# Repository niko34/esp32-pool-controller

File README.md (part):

<h1> ESP32 Pool Controller</h1>

Disclaimer : projet en cours de construction.

Contrôleur automatique de piscine basé sur ESP32 :
- mesure : température, pH, ORP
- pilotage : pompe de filtration, éclairage
- correction avec pompes doseuses : pH et ORP
- interfaces : application web locale, MQTT, API

## 🎯 Fonctionnalités

### Mesures et Contrôle
- **pH** : Mesure via module numérique Atlas Scientific **EZO pH** (I²C). La température de l'eau est transmise au module pour la compensation de température de la mesure.
- **ORP (Redox)** : Mesure via module numérique Atlas Scientific **EZO ORP** (I²C)
- **Température** : Deux sondes Dallas **DS18B20** (eau + circuit/boîtier), identification automatique des rôles sur le bus OneWire
- **Historique** : Historique des mesures
- **Mode d'installation** : Décrit le câblage réel du contrôleur et garantit qu'aucun produit n'est injecté sans circulation d'eau — *PoolController pilote la filtration* (sortie 12 V), *Alimenté par le circuit de filtration*, ou *Filtration externe signalée* (une domotique tierce signale l'état via HTTP/MQTT ; dosage suspendu sans signal récent)
- **Filtration** : Programmation automatique en fonction de la température de l'eau, programmation horaire, manuel
- **Eclairage** : Programmation horaire, manuel
- **Régulation automatique de pH et ORP** : Injection de produit de correction (pH-, chlore liquide) par **régulation proportionnelle temporisée (P)** avec pause de mélange et contrôle de débit PWM. Les mesures sont **lissées** (médiane + EMA) avant d'alimenter la régulation. *(pH+ : option de configuration présente mais non gérée actuellement.)*
- **Consommation de produits** : Estimation de la consommation de produit
- **Application Web locale** : Configuration et visualisation temps réel. Accessible sur le réseau Wifi configuré (`http://poolcontroller.local`) ou un réseau Wifi de en mode point d'accès (`http://192.168.4.1`). Aucune dépendance au Cloud. [Voir les screenshots](screenshots/)
- **API** : Toutes les fonctionnalités sont exposées avec une API
- **MQTT** : Exposition des données sur MQTT. Auto-discovery HomeAssistant.
- **Mise à jour OTA** : Mise à jour firmware via interface web

### Sécurité
- ⚠️ **Limites journalières** : Protection contre le surdosage
- ⚠️ **Limites horaires** : Temps maximum d'injection par heure configurable
- ⚠️ **Watchdog** : Redémarrage automatique en cas de blocage du système (30s)
- ⚠️ **Alertes MQTT** : Notifications en cas d'anomalie

## 📋 Matériel Requis

### Module ESP32 — ⚠️ PSRAM requise

Utiliser un **ESP32-DevKitC-VE** (module **WROVER-E**, ESP32 classique **avec 8 Mo de PSRAM**) — cf. `kicad/esp32-pool-controller/BOM.xlsx`, repère U2.

> ⚠️ **Pourquoi la PSRAM est nécessaire** : la **mise à jour en ligne depuis GitHub**
> (onglet Système → « Vérifier les mises à jour ») ouvre une session TLS qui réclame
> plusieurs blocs de mémoire contigus d'environ 16 Ko. Sur un module **sans PSRAM**
> (WROOM-32), la RAM interne ne les fournit plus de façon fiable une fois le système
> démarré : la vérification échoue de manière intermittente (`BIGNUM - Memory
> allocation failed`). Avec la PSRAM, ces allocations y sont placées automatiquement
> (seuil 4 Ko) et la fonction redevient fiable.
>
> Le firmware **fonctionne** sur un WROOM-32 sans PSRAM (binaire unique, détection
> automatique au démarrage, dégradation gracieuse — depuis la v2.18.0) : régulation,
> interface web, MQTT et **mise à jour manuelle par upload de fichier** restent
> pleinement opérationnels. Seule la vérification/installation automatique depuis
> GitHub est concernée.
>
> Modules déconseillés : l'**ESP32-S3** n'est pas supporté (architecture différente,
> brochage incompatible avec le PCB v2 — les GPIO 22 et 25 utilisés par l'I²C et la
> pompe pH n'y existent pas).

### PCB

Les **sources** KiCad sont versionnées dans [`kicad/`](kicad/) :

- [Schéma électronique](screenshots/Schema.png)
- [PCB](screenshots/PCB.png)
- `kicad/esp32-pool-controller/esp32-pool-controller.kicad_sch` — schéma
- `kicad/esp32-pool-controller/esp32-pool-controller.kicad_pcb` — routage
- `kicad/esp32-pool-controller/BOM.xlsx` — nomenclature (source ; le `BOM.csv`
  s'en déduit avec `python3 tools/bom_export.py`)

Les **fichiers de fabrication** (gerbers, perçage) ne sont pas versionnés : ils se
régénèrent avec `./scripts/build-gerbers.sh` (carte v2) ou `./scripts/build-jlcpcb.sh` (cartes v3, avec la liste des pièces et les positions) et sont publiés comme assets des
releases `pcb-vX`. Voir « Fichiers générés et releases » dans `CLAUDE.md`.

### Boîtier

Le boîtier imprimé en 3D est décrit par un script qui le construit en entier : voir [`boitier/`](boitier/README.md). Les fichiers FreeCAD, STEP et STL qu'il produit ne sont pas versionnés ; ils se régénèrent.

## 🧭 Reprendre le projet

Cette section s'adresse à quiconque récupère le dépôt — y compris son auteur dans
deux ans. Elle dit **où est quoi** et **comment on travaille ici**.

### Outils nécessaires

| Outil | Pour quoi | Indispensable ? |
|---|---|---|
| **PlatformIO** | compiler, téléverser, lancer les tests | oui |
| **Node.js** | `minify.js`, appelé par `build_fs.sh` | oui |
| **Chrome / Chromium** | générer les PDF de documentation | pour les releases |
| **`gh`** (GitHub CLI) | publier les releases | pour les releases |
| **KiCad 7+** | ouvrir le PCB, générer les gerbers | pour le matériel |
| **Python 3** | `tools/*.py` (BOM, coredump, couverture) | ponctuel |

⚠️ Sur macOS, `kicad-cli` et Chrome ne sont pas dans le `PATH` : les scripts
`scripts/*.sh` sondent aussi les emplacements `.app`.

### Repartir d'un clone (conteneur, autre machine)

```bash
# Debian / Ubuntu
sudo apt install -y python3 python3-pip nodejs npm chromium imagemagick zip gh
pip install --user platformio
# facultatif, seulement pour le PCB :
sudo apt install -y kicad

git clone https://github.com/niko34/esp32-pool-controller.git
cd esp32-pool-controller
pio pkg install -e esp32dev_core3   # télécharge la plateforme et les libs
pio test -e native                  # doit être vert
pio run                             # doit compiler
```

**Ce qui fonctionne depuis un clone nu** : les agents, les skills et les
commandes, les specs, les tests natifs, la compilation, la génération des PDF et
celle des gerbers. **Trois workflows GitHub Actions rejouent les trois premiers à
chaque push et à chaque PR** — tests natifs + couverture, compilation
`pio run -e esp32dev_core3`, et hygiène des specs (`./tools/check_specs.sh`,
lançable en local) : ce n'est pas une promesse, c'est une preuve. Voir
[docs/BUILD.md](docs/BUILD.md#intégration-continue-github-actions). Les scripts détectent leurs outils et échouent avec un message explicite
si l'un manque.

**Ce qui ne fonctionne pas à distance** : le déploiement sur l'appareil. Son mot
de passe n'est pas dans le dépôt — délibérément — et il vit sur un réseau local.
Il faut être sur le même réseau, et fournir le mot de passe :

```bash
./ota_update.sh firmware <adresse-ip> <mot-de-passe>
```

**Confort dégradé** : `.claude/settings.local.json` n'est pas versionné (il
contient des chemins absolus propres à une machine). Le `settings.json` partagé
couvre l'essentiel — y compris les garde-fous `deny` et `ask` — mais vous
confirmerez plus de commandes qu'en local. C'est le prix d'une configuration
qui ne présume rien de la machine.

### Où est quoi

```
src/            firmware C++ (ESP32, Arduino)      data/     interface web (vanilla JS)
test/           tests natifs — logique pure         docs/     doc technique, ADR, guides
specs/          LA SOURCE DE VÉRITÉ des demandes    kicad/    sources du PCB
scripts/        livrables de release (PDF, gerbers) tools/    utilitaires de développement
.claude/        agents, skills et commandes         builds/   archive LOCALE des binaires
```

### Comment on travaille

Le cycle est décrit en détail dans **[CLAUDE.md](CLAUDE.md)**. En résumé :

1. **Une demande = une spec** dans `specs/features/todo/`, au format du template.
   Elle se déplace vers `doing/` quand le travail commence, `done/` quand il finit,
   enrichie des notes techniques et des décisions prises.
2. **Le travail passe par des agents spécialisés** (`.claude/agents/`) :
   conception, implémentation firmware ou web, tests, revue, documentation.
   ⚠️ **`pool-chemistry` est obligatoire** dès qu'on touche au dosage, à la
   régulation ou à la calibration des sondes — ce sont les pompes qui injectent de
   l'acide et du chlore dans un bassin.
3. **Les tests natifs sont non négociables** : `pio test -e native` doit rester
   vert, et tout test neuf est **validé par mutation** — on casse volontairement le
   code qu'il protège pour vérifier qu'il meurt. Plusieurs défauts réels de ce
   projet n'ont été trouvés que comme ça.
4. **Toute décision structurante devient un ADR** dans `docs/adr/`. Les ADR sont
   immuables : on les amende d'une bannière, on ne réécrit pas leur histoire.

### Les commandes utiles

```bash
pio run                    # compiler (env unique esp32dev_core3)
pio test -e native         # 33 suites, ~1 286 cas
./build_fs.sh              # construire le filesystem web
./deploy.sh all            # flasher par USB (firmware + filesystem)
./deploy.sh ota-firmware   # mettre à jour par WiFi
./tools/coverage.sh        # couverture des tests
/release                   # publier une version firmware + doc
/release-pcb               # publier des fichiers de fabrication PCB
```

Il n'y a **qu'un seul environnement matériel**, `esp32dev_core3`. L'ancien repli
core Arduino 2.x a été retiré en v2.42.1 : il n'était plus compilable, plus
flashable, et aucun binaire de secours n'avait jamais été archivé
([ADR-0069](docs/adr/0069-retrait-repli-core-2.md)).

### Ce qui n'est pas dans le dépôt, et pourquoi

Les **fichiers générés** n'y sont pas : PDF de documentation, gerbers de
fabrication, firmware compilé. Ils sont attachés aux **releases GitHub**, où ils
sont horodatés et associés à un tag. Voir « Fichiers générés et releases » dans
[CLAUDE.md](CLAUDE.md).

**Deux exceptions volontaires**, parce que ces fichiers ne sont pas *générés* mais
*relevés* — rien ne les régénère :

- **`docs/incidents/`** — les coredumps de production et leurs traces décodées. Un
  coredump n'existe qu'une fois : il est écrasé au crash suivant.
- **L'ELF est attaché à chaque release** (~29 Mo) en plus du `.bin`. `esp-coredump`
  vérifie le SHA256 de l'image et refuse un ELF qui ne correspond pas : sans celui
  de la version exacte, un crash reste indéchiffrable.

`builds/` contient l'archive **locale** des ELF de tous les builds (2,6 Go) et
n'est pas versionné.

Le **générateur du boîtier** est dans [`boitier/`](boitier/README.md) ; ses sorties (FreeCAD, STEP, STL) ne sont pas versionnées.

## 🚀 Installation

### PlatformIO (Recommandé)

1. **Cloner le projet**
   ```bash
   git clone https://github.com/niko34/esp32-pool-controller.git
   cd esp32-pool-controller
   ```

2. **Ouvrir avec VS Code + PlatformIO**
   ```bash
   code .
   ```

3. **Compiler et déployer**

   L'unique environnement de build est **`esp32dev_core3`** (core Arduino 3.x / ESP-IDF 5 via pioarduino) — bootloader **et** application, depuis la v2.20.4 ([ADR-0042](docs/adr/0042-core3-environnement-par-defaut.md)). L'environnement de repli core 2 a été retiré en v2.42.1 ([ADR-0069](docs/adr/0069-retrait-repli-core-2.md)) :

   ```bash
   pio run                              # core 3, env unique
   ./deploy.sh all                      # firmware + filesystem
   ```

   ℹ️ Premier build sur une machine neuve : `pio pkg install -e esp32dev_core3` (téléchargement du framework). Voir [BUILD.md](docs/BUILD.md#lenvironnement-firmware-unique).

   **Via USB** (obligatoire pour la première installation, et pour tout changement de bootloader ou de table de partitions) :
   ```bash
   ./deploy.sh all       # Compile et upload firmware + filesystem
   ./deploy.sh firmware  # Firmware uniquement
   ./deploy.sh fs        # Filesystem uniquement
   ```

   **Via WiFi OTA** (mises à jour suivantes, une fois la première installation USB effectuée) :
   ```bash
   ./deploy.sh ota-all       # Compile et envoie firmware + filesystem
   ./deploy.sh ota-firmware  # Firmware uniquement
   ./deploy.sh ota-fs        # Filesystem uniquement
   ```

   Voir [UPDATE_GUIDE.md](docs/UPDATE_GUIDE.md) pour plus de détails sur les méthodes de mise à jour.

4. **Moniteur série**
   ```bash
   pio device monitor -b 115200
   ```

### Première connexion et accès à l'interface Web

1. **Première connexion**
   - Au démarrage, l'ESP32 crée un point d'accès WiFi `PoolControllerAP`
   - Le mot de passe WiFi AP est **unique par appareil**, généré aléatoirement au premier boot et stocké en NVS
   - Il s'affiche en clair dans le moniteur série **tant que le wizard de configuration n'est pas complété** :
     ```
     [INFO] AP démarré: PoolControllerAP
     [INFO] AP Password: XXXXXXXX
     [INFO] IP AP: 192.168.4.1
     ```
   - Le flash USB (`./deploy.sh all`) **enchaîne le moniteur série** : l'ouverture du port redémarre l'ESP32, le boot est donc capté depuis sa première ligne, sans manœuvre particulière
   - Coller le mot de passe sur une étiquette sur le boîtier
   - Se connecter au réseau `PoolControllerAP` avec ce mot de passe et accéder à l'assistant de configuration http://192.168.4.1

   > **Après le wizard complété**, si l'AP redémarre (ex : perte WiFi), le mot de passe n'est plus affiché en clair dans les logs pour des raisons de sécurité. Utiliser l'étiquette ou l'API :
   > ```
   > GET http://poolcontroller.local/auth/ap-password
   > ```

   > **Forcer la génération d'un nouveau mot de passe AP** (ex : fabrication d'un nouvel appareil, remplacement d'étiquette) : utiliser l'option `factory`, qui efface la flash, réinstalle, ré-efface la NVS **en dernier**, puis **ouvre le moniteur série automatiquement**. Le mot de passe s'affiche dans les premières lignes de boot — inutile d'ouvrir un moniteur à la main, et inutile de le lancer *avant* d'alimenter l'appareil.
   > ```bash
   > ./deploy.sh factory
   > ```
   > ```
   > === MOT DE PASSE AP WIFI: XXXXXXXX ===
   > ```
   > ⚠️ Efface **toute** la flash (firmware, filesystem, NVS, historique). À n'utiliser que sur un appareil qu'on réinitialise complètement. Voir [UPDATE_GUIDE.md](docs/UPDATE_GUIDE.md#récupérer-le-mot-de-passe-wifi-ap).

2. **Accès interface web**
   - `http://poolcontroller.local` si réseau wifi configuré, sinon se connecter au réseau AP PoolControllerAP et utiliser l'adresse http://192.168.4.1
   - Onglets disponibles:
     - **Tableau de bord** : Visualisation temps réel pH/ORP/Température
     - **Filtration** : Contrôle et programmation de la pompe de filtration
     - **Éclairage** : Contrôle et programmation de l'éclairage
     - **Température** : Historique et calibration de la sonde de température
     - **pH** : Mesure, historique, calibration et réglages dosage pH
     - **ORP** : Mesure, historique, calibration et réglages dosage chlore
     - **Produits** : Suivi de la consommation des produits chimiques
     - **Paramètres** : WiFi, MQTT, heure, sécurité, régulation, système

### Calibration Capteurs

#### Calibration pH (Atlas Scientific EZO pH)

La calibration est gérée **en interne par le module EZO** (commandes I²C `Cal,...`), mémorisée dans le module lui-même — il n'y a ni offset/pente stockés côté ESP32, ni EEPROM, ni librairie analogique. Elle se déclenche depuis l'interface web, onglet **pH** → carte **Calibration** (deux sous-blocs indépendants). Le module EZO pH accepte les points **milieu (pH 7.0)**, **bas (pH 4.0)** et, optionnellement, **haut**. La régulation automatique du pH est **inhibée tant que les 2 points (mid + low) ne sont pas calibrés**.

**Calibration via l'interface web** :
1. Aller dans l'onglet **pH** → carte **Calibration**
2. Rincer la sonde à l'eau distillée, la plonger dans la solution tampon **pH 7.00**, attendre stabilisation (~1 min)
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
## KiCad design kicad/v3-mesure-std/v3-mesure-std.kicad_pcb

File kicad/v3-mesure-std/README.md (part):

# Carte de mesure du PCB v3, à composants courants — composants et connexions

Carte de mesure **retenue pour le v3** (décision D8 de
[feature-215](../../specs/features/todo/feature-215-conception-du-pcb-v3.md), 2026-11-25) :
sans module Atlas, tous les composants posés par l'atelier, chacun avec un équivalent d'un
autre fabricant. L'étude et les relectures sont dans
[feature-217](../../specs/features/todo/feature-217-carte-de-mesure-a-composants-courants.md).

La première étude, à modules Atlas (`kicad/v3-mesure/`), a été **retirée du dépôt le
2026-11-26** : elle reste dans l'historique git (dernier état : commit `5eb6b3d`). Ce qui en
restait valable est recopié plus bas, dans « Repris de l'étude à modules Atlas ».

✅ **État au 2026-11-25 : schéma (rév. 0.2) et carte placée et routée (rév. 0.1) écrits par
script, relus par `electronics-reviewer` — aucune erreur. Pas encore ouverts dans KiCad par
l'utilisateur.**

🆕 **Rév. 0.3 du 2026-11-28 — étude des parasites et de la fiabilité** (demande de l'utilisateur).
Quatre changements sur l'entrée de chaque voie, détaillés en fin de fiche : un **filtre devant le
convertisseur**, le **corps de la prise protégé des décharges**, la **garde pilotée à travers une
résistance et découverte de son vernis**, et l'**alimentation de l'amplificateur pH filtrée**.
Les règles à tenir désormais, avec leurs raisons, sont dans
[`../REGLES-CEM-ET-FIABILITE.md`](../REGLES-CEM-ET-FIABILITE.md) ;
`python3 scripts/verifier_regles_cartes.py v3-mesure-std` les contrôle.
Schéma et carte sont tous deux en rév. 0.3, régénérés par leurs scripts.

## Les fichiers de ce dossier

| Fichier | Rôle |
|---|---|
| `generer_schema.py` | écrit le schéma depuis le tableau ci-dessous. ⚠️ Le relancer **réécrit** le schéma en entier |
| `v3-mesure-std.kicad_sch` | le schéma, format A2 : les deux voies à gauche, le connecteur J1 à droite |
| `v3-mesure-std.kicad_sym`, `sym-lib-table` | les symboles propres à la carte |
| `generer_carte.py` | écrit la carte depuis la netlist du schéma : placement, pistes, plans. ⚠️ Le relancer **réécrit** la carte en entier |
| `v3-mesure-std.kicad_pcb` | la carte, 73 × 54 mm, quatre couches |
| `v3-mesure-std.pretty/`, `fp-lib-table` | empreintes propres : module d'alimentation, prise BNC, trou de fixation |
| `v3-mesure-std.kicad_pro`, `v3-mesure-std.kicad_dru` | le projet, ses classes de fils et ses règles d'isolement |

Pour régénérer :
`kicad-cli sch export netlist -o /tmp/n.net v3-mesure-std.kicad_sch` puis
`python3 generer_carte.py /tmp/n.net`.

## La carte (2026-11-25)

Même contour que la carte à modules Atlas : 73 × 54 mm, prises BNC à l'entraxe de 36,3 mm
sur le bord du bas, J1 en haut, quatre trous M3. Couches : composants et signaux dessus,
masse au-dessous, alimentation, puis masse et quelques pistes sur la face du dessous.

**La barrière d'isolation**
- Zone interdite au cuivre de **3,0 mm** sur les quatre couches entre le côté ESP32 et chaque
  voie : c'est la distance entre les deux rangées de pastilles de l'ISO1540.
- Au droit du module d'alimentation elle se réduit à un col : ses broches 2 et 3 sont au pas
  de 2,54 mm, soit **0,94 mm de cuivre à cuivre**, que rien ne peut élargir.
- Entre la voie pH et la voie ORP : 3,0 mm.
- ℹ️ La carte à modules Atlas avait 5 mm partout (imposés par l'ADM3260). Ici la barrière
  est **fonctionnelle** : elle ne voit que quelques volts, la sécurité secteur vient de
  l'alimentation (D4). 1 500 V est l'essai d'une minute du module. Relu et jugé cohérent.

**L'entrée de la sonde**
- pH : anneau de garde sur le dessus, relié aux broches 2 et 7 de U104, qui entoure l'âme de
  la prise, R105 et la broche 1 ; garde en plein sur les trois autres couches, sous l'entrée.
  Piste d'entrée de 2,1 mm, piste de l'âme de 6,1 mm.
- ORP : même anneau, relié à `MESURE_ORP`, refermé sous le boîtier entre la broche 4 (masse)
  et la broche 5 (entrée).
- ~~**Vernis conservé** sur l'anneau et l'entrée (point P6 fermé).~~ ⚠️ **Revu le 2026-11-28
  (rév. 0.3) : le vernis est retiré sur la garde**, là où rien n'est posé dessus. Le calcul
  d'origine (0,0003 pH pour 1 GΩ de fuite) supposait que la fuite allait vers la garde. Or une
  fuite **en surface du vernis** passe par-dessus un anneau enterré sans le rencontrer, et va de
  l'âme au corps de la prise : avec 1 GΩ et une sonde de 250 MΩ, c'est 20 % d'erreur de pente.
  Le fabricant de l'amplificateur le demande (fiche du LMP7721, § 10.1 : pas de vernis sur
  l'entrée ni sur la garde). Le cuivre découvert est doré par l'atelier, il n'est pas nu.
  ⛔ Aucune ouverture sous la prise, côté dessus : son corps métallique y est posé.
- **Rév. 0.3** : l'amplificateur et la résistance d'entrée sont remontés de 1,5 mm. La pastille
  « âme » de R105 était à 0,58 mm du corps de la prise ; elle en est à 2,1 mm (1,78 mm de son
  encombrement dessiné). Deux doigts de garde descendent de l'anneau entre l'âme et le corps.
- Le trait d'encre de la prise BNC qui passait sur l'âme et l'anneau est retiré de l'empreinte.
- Le corps de la prise est relié par une zone de cuivre `REF` sur le dessus.

**Deux pistes passent par la face du dessous** : SCL côté isolé, sur 3 mm, pour croiser
SDA ; et, sur la voie ORP, la liaison de R208 au corps de la prise. Sans effet sur la mesure.

### Ce qui est vérifié
- Contrôle des règles (`kicad-cli pcb drc --severity-all --schematic-parity`) : 0 violation,
  0 liaison manquante, 0 écart avec le schéma. Les seuls messages portent sur des
  bibliothèques absentes de la machine de génération.
- Les protections ont été éprouvées par des fautes volontaires : via dans la barrière,
  condensateur non relié, piste qui franchit la barrière, court-circuit masse / entrée du pH
  — toutes détectées. ℹ️ Un plan de cuivre débordant sur la séparation des voies n'est pas
  signalé : la zone interdite le rogne d'elle-même.
- Relecture du tracé : découplages à 1,2 à 2 mm de leur broche ; régulateur à +7 à +13 °C ;
  module d'alimentation à 13,7 mm de l'entrée du pH ; pistes, écarts et vias dans les
  capacités de l'atelier ; rien n'est posé sur la face du dessous.

- **Rév. 0.3, 2026-11-28** : même contrôle, 0 erreur, 0 liaison manquante, 0 écart avec le
  schéma. Cinq avertissements **attendus** « piste sans suite » : les deux doigts de garde de
  chaque voie et la traverse de la voie ORP. `scripts/verifier_regles_cartes.py v3-mesure-std` :
  toutes les règles tenues ; l'isolement y est **remesuré sur le cuivre**, sans passer par les
  règles de KiCad : 0,94 et 0,95 mm aux broches des modules d'alimentation, 3,5 mm entre les voies.
  ⚠️ Six réseaux nouveaux n'étaient dans aucune famille : la règle d'isolement de KiCad ne les
  voyait pas. Ajoutés ; c'est maintenant contrôlé (règle M1).

### Ce qui n'est PAS vérifié
- L'ouverture de la carte dans le KiCad de l'utilisateur.
- **L'empreinte du module d'alimentation face à la pièce réelle** : dessinée d'après le plan
  d'implantation des fiches Evisun et Ylptec (corps de 11,7 × 6 mm d'un seul côté de la
  rangée de broches, broche 1 à 2,03 mm du bout). Le relecteur n'a pas pu afficher le dessin.
  Si le corps était de l'autre côté, il reposerait sur C101.
- L'empreinte de la prise BNC face au plan du fabricant (déjà ouvert sur la carte Atlas).
- L'empilement des couches de l'atelier.

## Repris de l'étude à modules Atlas (2026-11-24)

**Disposition.** La carte est montée à l'horizontale et les deux prises BNC, **coudées**,
sortent par le grand bord du bas. Entraxe de **36,3 mm** : celui des deux perçages que le
boîtier avait déjà. Le connecteur J1 et le côté ESP32 sont à l'opposé, en haut.

**La prise** : `C521219`, dosinconn DOSIN-801-0080, embase BNC femelle coudée, traversante.
Plan du fabricant (révision A) lu le 2026-11-24 :

| Ce que dit le plan | Valeur |
|---|---|
| Corps | **laiton nickelé, donc métallique** ; isolant en téflon |
| Fixation | nez fileté **M12 × 0,75**, avec écrou et joint : la prise se serre sur la paroi |
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
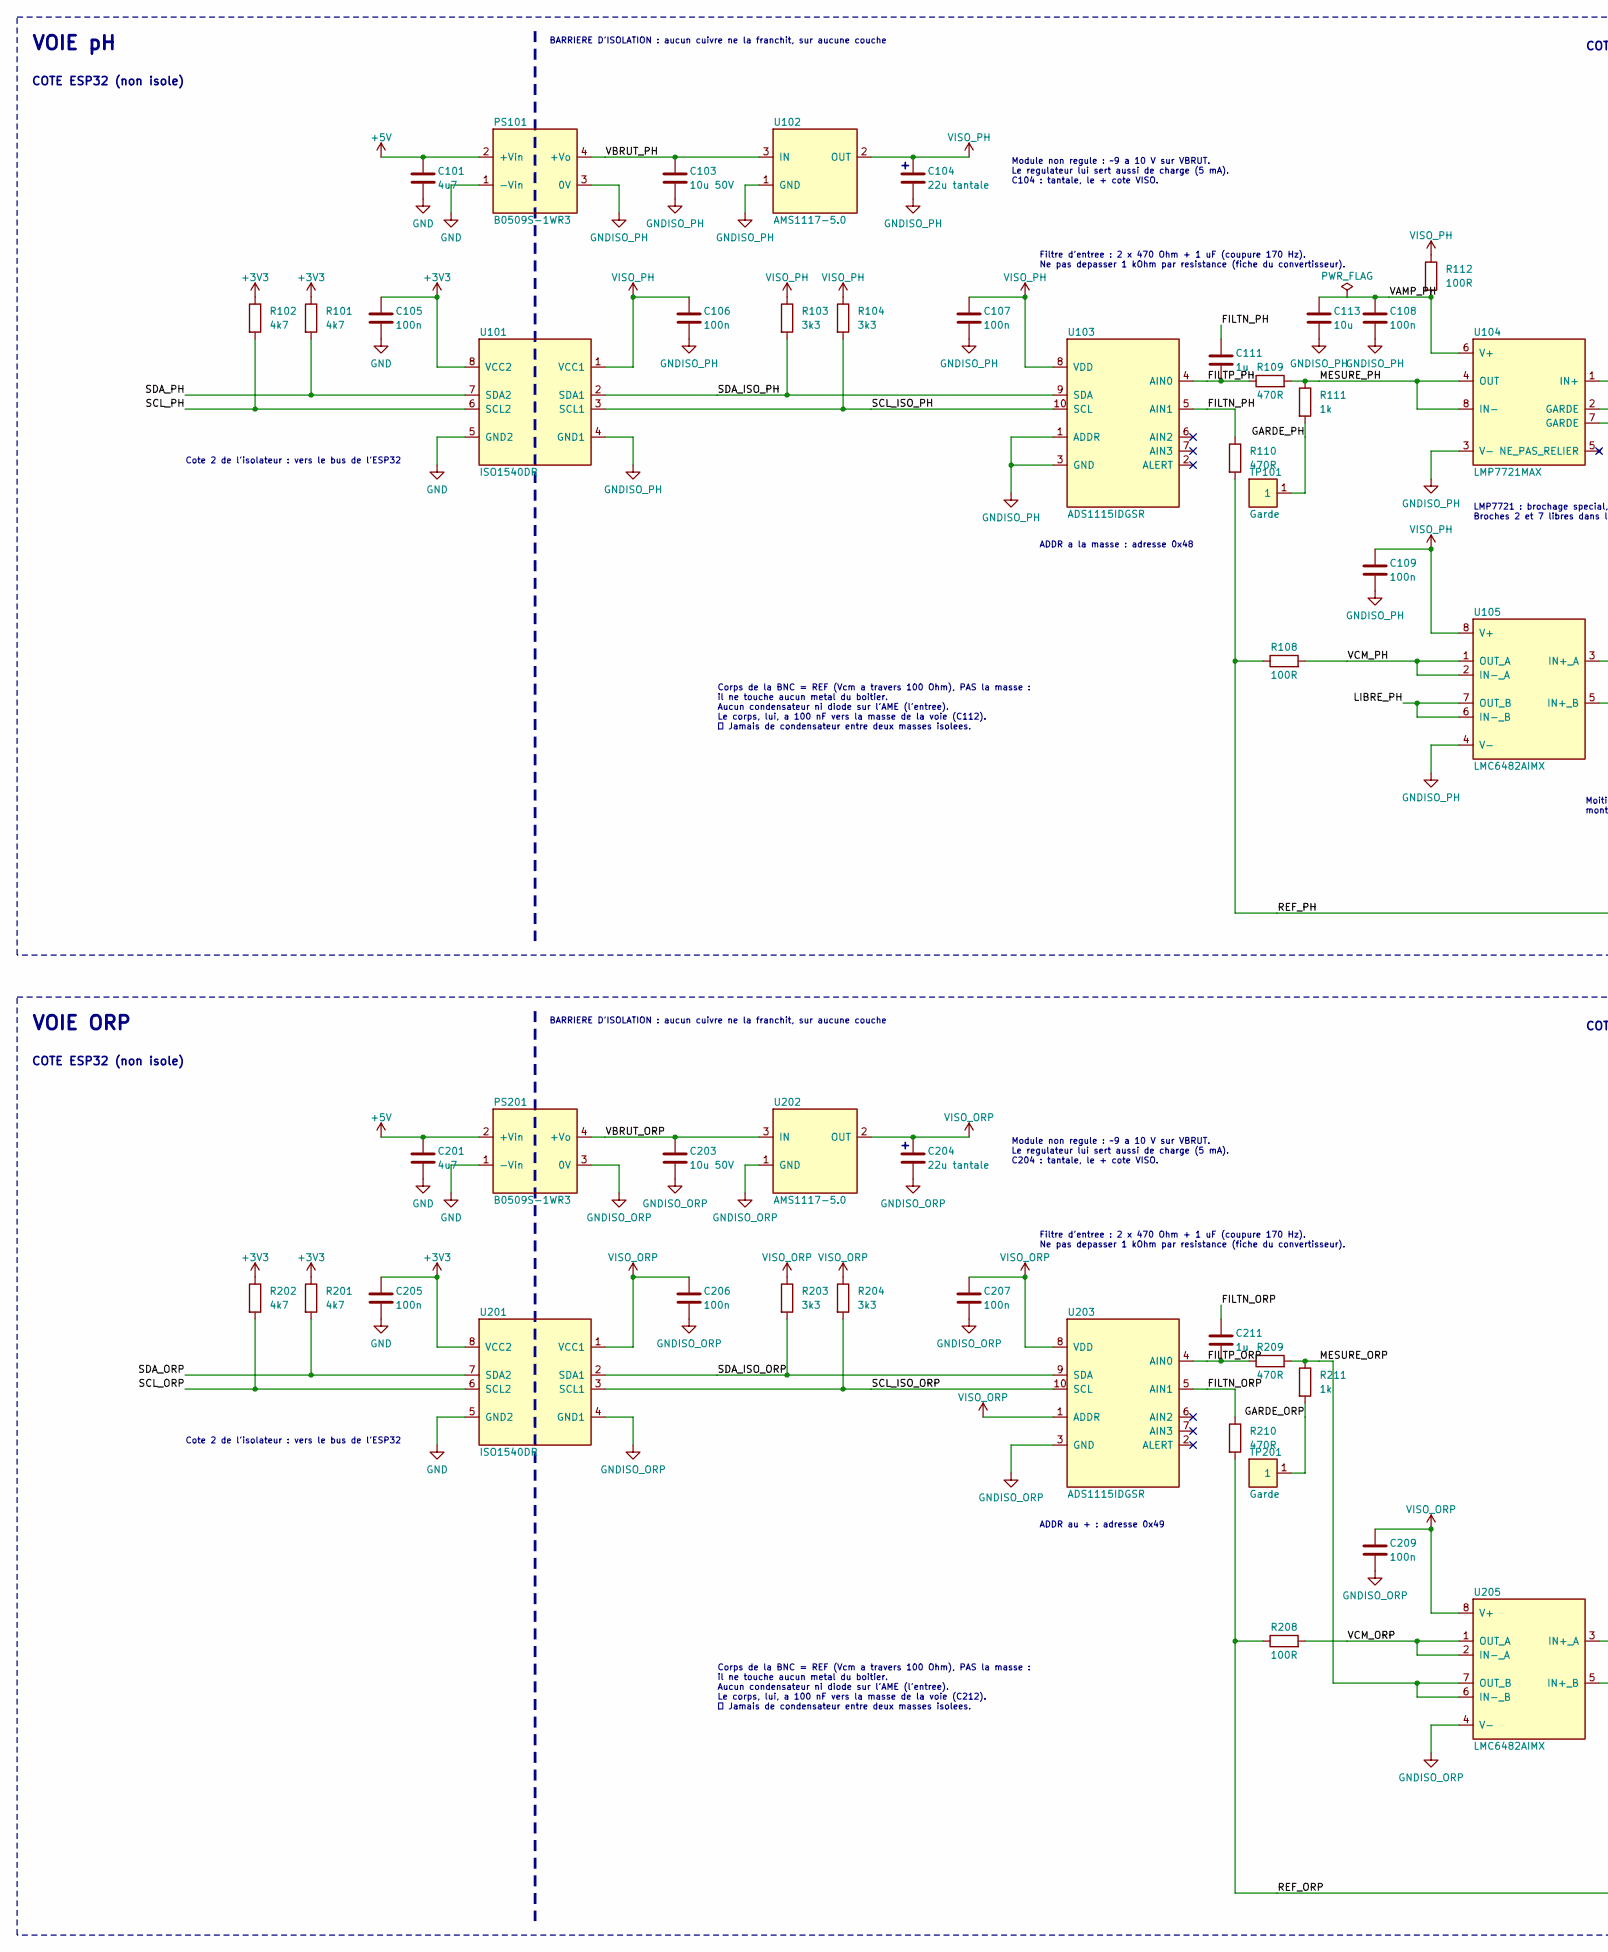
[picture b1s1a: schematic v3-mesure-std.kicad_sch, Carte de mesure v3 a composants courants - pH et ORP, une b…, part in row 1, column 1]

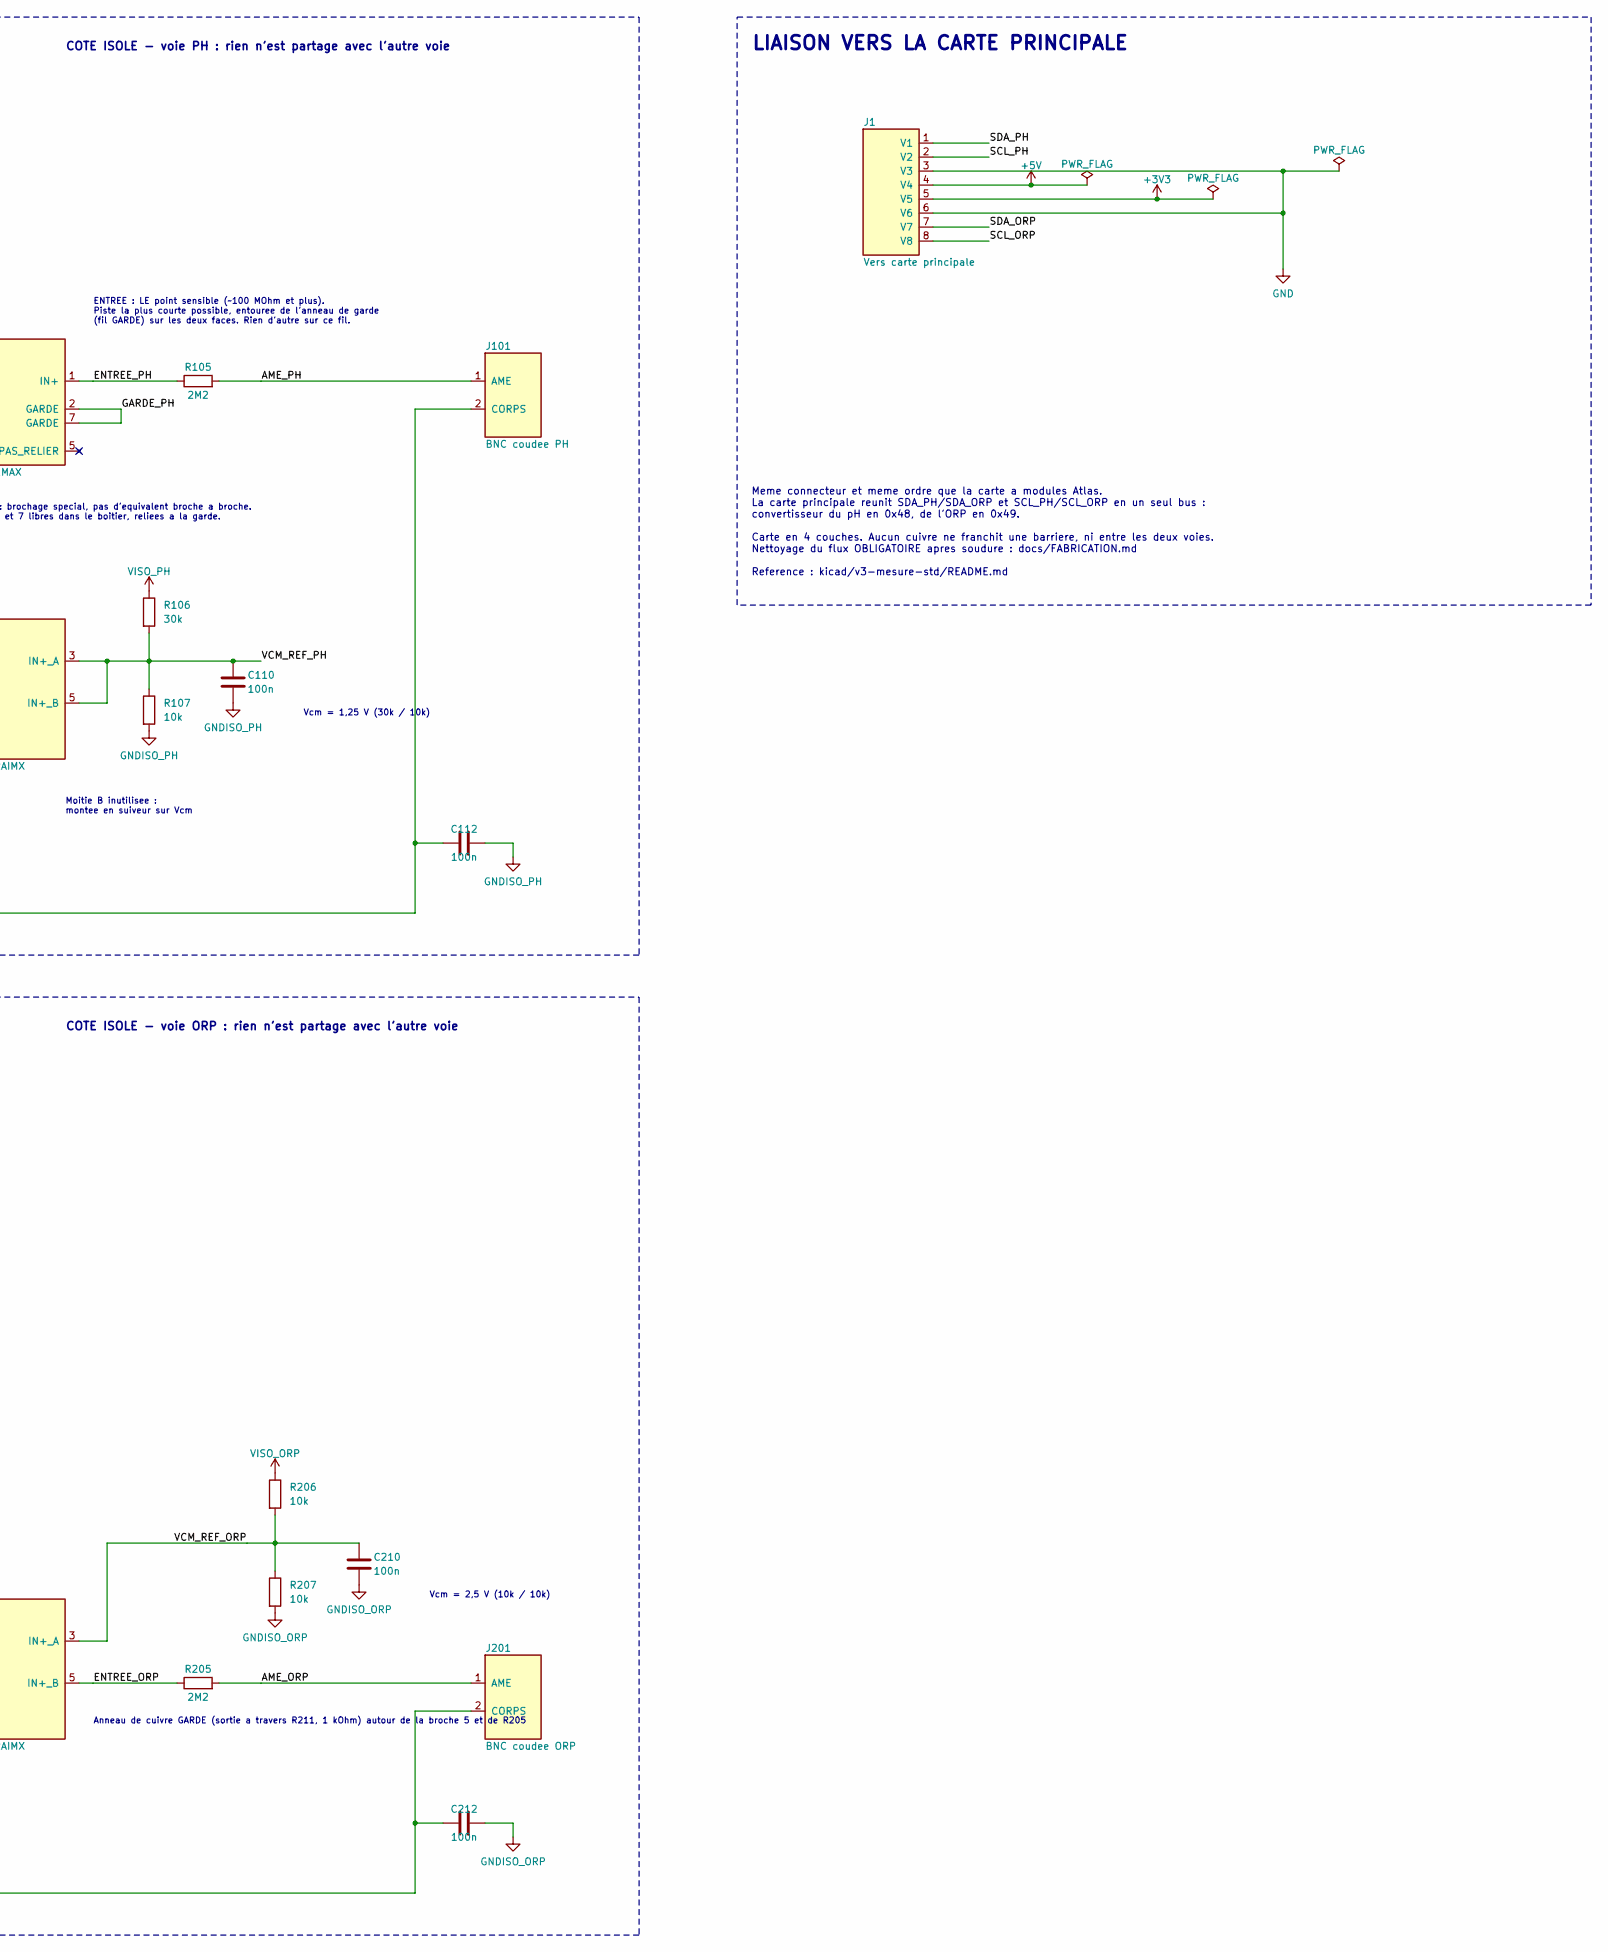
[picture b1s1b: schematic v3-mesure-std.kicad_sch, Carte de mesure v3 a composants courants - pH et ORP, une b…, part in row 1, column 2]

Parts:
C101, C201: 4u7; C_0805_2012Metric; LCSC C1779
C103, C203: 10u 50V; C_1206_3216Metric; LCSC C13585
C104, C204: 22u tantale; CP_EIA-3528-21_Kemet-B; LCSC C8020
C105, C106, C107, C108, C109, C110, C112, C205, C206, C207, C209, C210, C212: 100n; C_0402_1005Metric; LCSC C1525
C111, C211: 1u; C_0603_1608Metric; LCSC C15849
C113: 10u; C_0805_2012Metric; LCSC C15850
J1: Vers carte principale; JST_XH_B8B-XH-A_1x08_P2.50mm_Vertical; LCSC C157972
J101: BNC coudee PH; BNC_Dosin_801-0080_Coudee; LCSC C521219
J201: BNC coudee ORP; BNC_Dosin_801-0080_Coudee; LCSC C521219
PS101, PS201: B0509S-1WR3; DCDC_SIP4_B05xxS-1W; LCSC C5369463
R101, R102, R201, R202: 4k7; R_0603_1608Metric; LCSC C23162
R103, R104, R203, R204: 3k3; R_0603_1608Metric; LCSC C22978
R105, R205: 2M2; R_0805_2012Metric; LCSC C26113
R106: 30k; R_0603_1608Metric; LCSC C22984
R107, R206, R207: 10k; R_0603_1608Metric; LCSC C25804
R108, R112, R208: 100R; R_0603_1608Metric; LCSC C22775
R109, R110, R209, R210: 470R; R_0603_1608Metric; LCSC C23179
R111, R211: 1k; R_0603_1608Metric; LCSC C21190
TP101, TP201: Garde; TestPoint_Pad_D1.0mm
U101, U201: ISO1540DR; SOIC-8_3.9x4.9mm_P1.27mm; LCSC C179739
U102, U202: AMS1117-5.0; SOT-223-3_TabPin2; LCSC C6187
U103, U203: ADS1115IDGSR; VSSOP-10_3x3mm_P0.5mm; LCSC C37593
U104: LMP7721MAX; SOIC-8_3.9x4.9mm_P1.27mm; LCSC C2864387
U105, U205: LMC6482AIMX; SOIC-8_3.9x4.9mm_P1.27mm; LCSC C12620

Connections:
+3V3: C105.1, C205.1, J1.5 (V5), R101.1, R102.1, R201.1, R202.1, U101.8 (VCC2), U201.8 (VCC2)
+5V: C101.1, C201.1, J1.4 (V4), PS101.2 (+Vin), PS201.2 (+Vin)
/AME_ORP: J201.1 (AME), R205.2
/AME_PH: J101.1 (AME), R105.2
/ENTREE_ORP: R205.1, U205.5 (IN+_B)
/ENTREE_PH: R105.1, U104.1 (IN+)
/FILTN_ORP: C211.1, R210.1, U203.5 (AIN1)
/FILTN_PH: C111.1, R110.1, U103.5 (AIN1)
/FILTP_ORP: C211.2, R209.1, U203.4 (AIN0)
/FILTP_PH: C111.2, R109.1, U103.4 (AIN0)
/GARDE_ORP: R211.2, TP201.1
/GARDE_PH: R111.2, TP101.1, U104.2 (GARDE), U104.7 (GARDE)
/LIBRE_PH: U105.6 (IN-_B), U105.7 (OUT_B)
/MESURE_ORP: R209.2, R211.1, U205.6 (IN-_B), U205.7 (OUT_B)
/MESURE_PH: R109.2, R111.1, U104.4 (OUT), U104.8 (IN-)
/REF_ORP: C212.1, J201.2 (CORPS), R208.1, R210.2
/REF_PH: C112.1, J101.2 (CORPS), R108.1, R110.2
/SCL_ISO_ORP: R204.2, U201.3 (SCL1), U203.10 (SCL)
/SCL_ISO_PH: R104.2, U101.3 (SCL1), U103.10 (SCL)
/SCL_ORP: J1.8 (V8), R202.2, U201.6 (SCL2)
/SCL_PH: J1.2 (V2), R102.2, U101.6 (SCL2)
/SDA_ISO_ORP: R203.2, U201.2 (SDA1), U203.9 (SDA)
/SDA_ISO_PH: R103.2, U101.2 (SDA1), U103.9 (SDA)
/SDA_ORP: J1.7 (V7), R201.2, U201.7 (SDA2)
/SDA_PH: J1.1 (V1), R101.2, U101.7 (SDA2)
/VAMP_PH: C108.1, C113.1, R112.2, U104.6 (V+)
/VBRUT_ORP: C203.1, PS201.4 (+Vo), U202.3 (IN)
/VBRUT_PH: C103.1, PS101.4 (+Vo), U102.3 (IN)
/VCM_ORP: R208.2, U205.1 (OUT_A), U205.2 (IN-_A)
/VCM_PH: R108.2, U105.1 (OUT_A), U105.2 (IN-_A)
/VCM_REF_ORP: C210.1, R206.2, R207.1, U205.3 (IN+_A)
/VCM_REF_PH: C110.1, R106.2, R107.1, U105.3 (IN+_A), U105.5 (IN+_B)
GND: C101.2, C105.2, C201.2, C205.2, J1.3 (V3), J1.6 (V6), PS101.1 (-Vin), PS201.1 (-Vin), U101.5 (GND2), U201.5 (GND2)
GNDISO_ORP: C203.2, C204.2, C206.2, C207.2, C209.2, C210.2, C212.2, PS201.3 (0V), R207.2, U201.4 (GND1), U202.1 (GND), U203.3 (GND), U205.4 (V-)
GNDISO_PH: C103.2, C104.2, C106.2, C107.2, C108.2, C109.2, C110.2, C112.2, C113.2, PS101.3 (0V), R107.2, U101.4 (GND1), U102.1 (GND), U103.1 (ADDR), U103.3 (GND), U104.3 (V-), U105.4 (V-)
VISO_ORP: C204.1, C206.1, C207.1, C209.1, R203.1, R204.1, R206.1, U201.1 (VCC1), U202.2 (OUT), U203.1 (ADDR), U203.8 (VDD), U205.8 (V+)
VISO_PH: C104.1, C106.1, C107.1, C109.1, R103.1, R104.1, R106.1, R112.1, U101.1 (VCC1), U102.2 (OUT), U103.8 (VDD), U105.8 (V+)

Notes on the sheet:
VOIE pH
COTE ESP32 (non isole)
COTE ISOLE - voie PH : rien n'est partage avec l'autre voie
BARRIERE D'ISOLATION : aucun cuivre ne la franchit, sur aucune couche
Module non regule : ~9 a 10 V sur VBRUT. Le regulateur lui sert aussi de charge (5 mA). C104 : tantale, le + cote VISO.
Cote 2 de l'isolateur : vers le bus de l'ESP32
ADDR a la masse : adresse 0x48
Filtre d'entree : 2 x 470 Ohm + 1 uF (coupure 170 Hz). Ne pas depasser 1 kOhm par resistance (fiche du convertisseur).
Moitie B inutilisee : montee en suiveur sur Vcm
Vcm = 1,25 V (30k / 10k)
ENTREE : LE point sensible (~100 MOhm et plus). Piste la plus courte possible, entouree de l'anneau de garde (fil GARDE) sur les deux faces. Rien d'autre sur ce fil.
LMP7721 : brochage special, pas d'equivalent broche a broche. Broches 2 et 7 libres dans le boitier, reliees a la garde.
Corps de la BNC = REF (Vcm a travers 100 Ohm), PAS la masse : il ne touche aucun metal du boitier. Aucun condensateur ni diode sur l'AME (l'entree). Le corps, lui, a 100 nF vers la masse de la voie (C112). ⛔ Jamais de condensateur entre deux masses isolees.
VOIE ORP
COTE ISOLE - voie ORP : rien n'est partage avec l'autre voie
Module non regule : ~9 a 10 V sur VBRUT. Le regulateur lui sert aussi de charge (5 mA). C204 : tantale, le + cote VISO.
ADDR au + : adresse 0x49
Vcm = 2,5 V (10k / 10k)
Anneau de cuivre GARDE (sortie a travers R211, 1 kOhm) autour de la broche 5 et de R205
Corps de la BNC = REF (Vcm a travers 100 Ohm), PAS la masse : il ne touche aucun metal du boitier. Aucun condensateur ni diode sur l'AME (l'entree). Le corps, lui, a 100 nF vers la masse de la voie (C212). ⛔ Jamais de condensateur entre deux masses isolees.
LIAISON VERS LA CARTE PRINCIPALE
Meme connecteur et meme ordre que la carte a modules Atlas. La carte principale reunit SDA_PH/SDA_ORP et SCL_PH/SCL_ORP en un seul bus : convertisseur du pH en 0x48, de l'ORP en 0x49. Carte en 4 couches. Aucun cuivre ne franchit une barriere, ni entre les deux voies. Nettoyage du flux OBLIGATOIRE a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

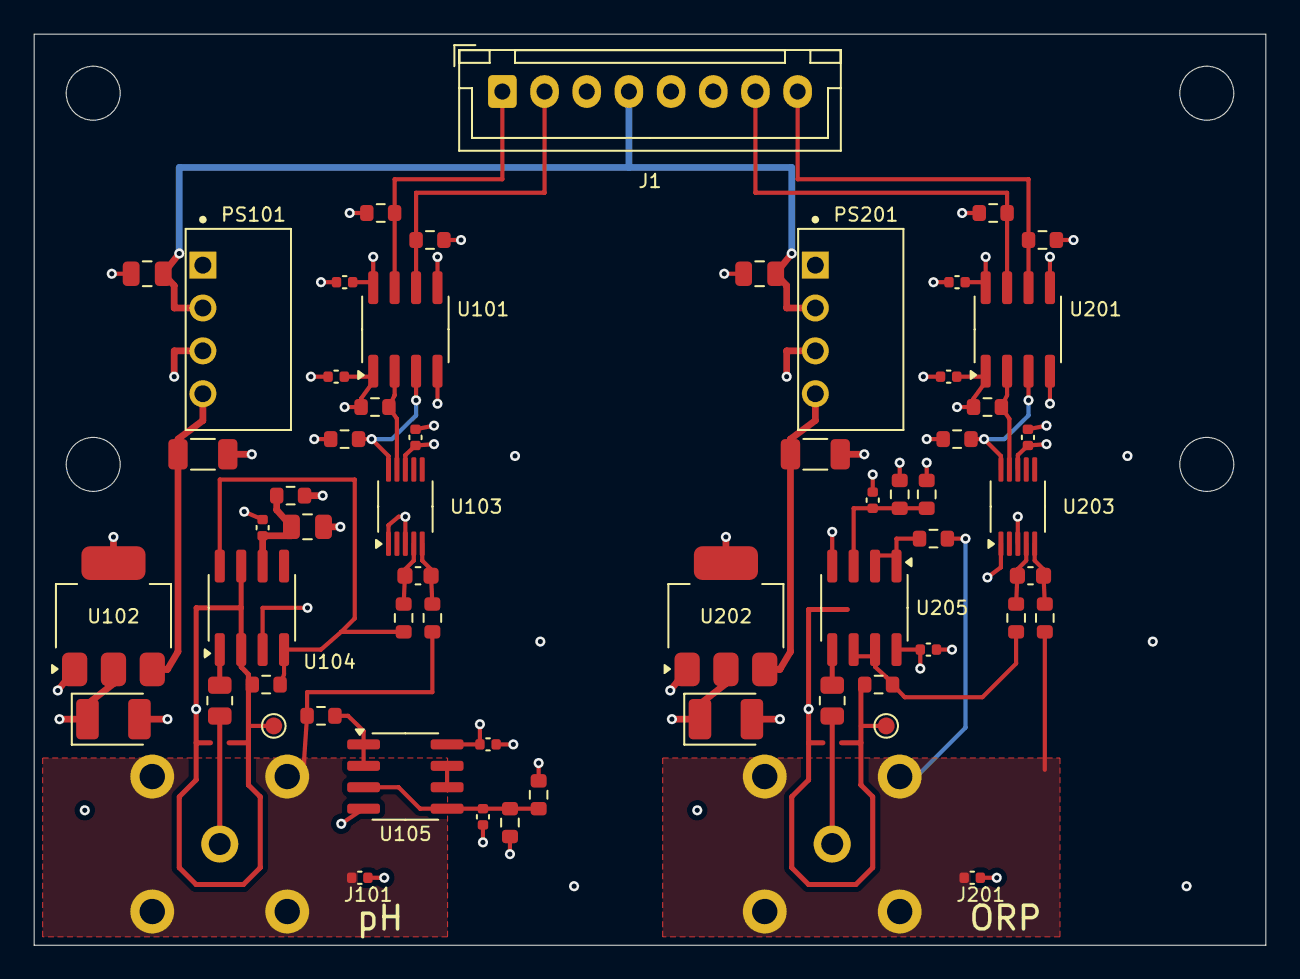
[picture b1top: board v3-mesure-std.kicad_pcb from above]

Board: 4 copper layers, 73.0 x 54.0 mm, 65 parts (0 on the bottom side), 37 nets.

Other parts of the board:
H1, H2, H3, H4: Trou_M3_NPTH

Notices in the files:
README.md:
📄 Licence:
MIT License - Voir fichier LICENSE
